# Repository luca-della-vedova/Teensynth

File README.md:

# Teensynth

The aim of the project is to create a companion board for MIDI compatible keyboards / electric pianos and augment them with commonly used / needed features such as:

* Midi recording: Sample and forward USB Midi signal and forward it to the host machine (or record in an SD card).
* Audio recording: Record Line out / Headphone out (for now only the latter is implemented) and stream it to the host through an Audio USB device interface.
* Midi synthesizer: Read MIDI files from SD card or receive MIDI commands from USB interface and synthesize them, as well as mix them with the audio signal (i.e. create a midi base and jam on it!)
* Implement pitch bend: For keyboards that support pitch bend MIDI commands but don't have a pitch wheel, create one with a joystick / potentiometer.

The board aims to be used in two ways:

### Standalone mode

All the recording outputs are to SD card, all the inputs (i.e. MIDI) are from SD card or firmware, control is done through hardware buttons and feedback to the user is through the Grove compatible I2C LCD display. 

### USB device mode

The device implements bidirectional MIDI (send the keyboard output to the host machine / synthesize the host machine's output) and Audio streaming to the host machine.
Streaming audio from the host machine to the onboard DAC should also be possible but is not a priority right now.

# Hardware

The hardware has been designed with kicad, it is a carrier board for  Teensy 4.1 and the Adafruit VS1053B breakout board.

# Firmware

The firmware has been developed with the Arduino / Teensyduino IDE, using external libraries (such as Adafruit VS1053B library) when necessary.

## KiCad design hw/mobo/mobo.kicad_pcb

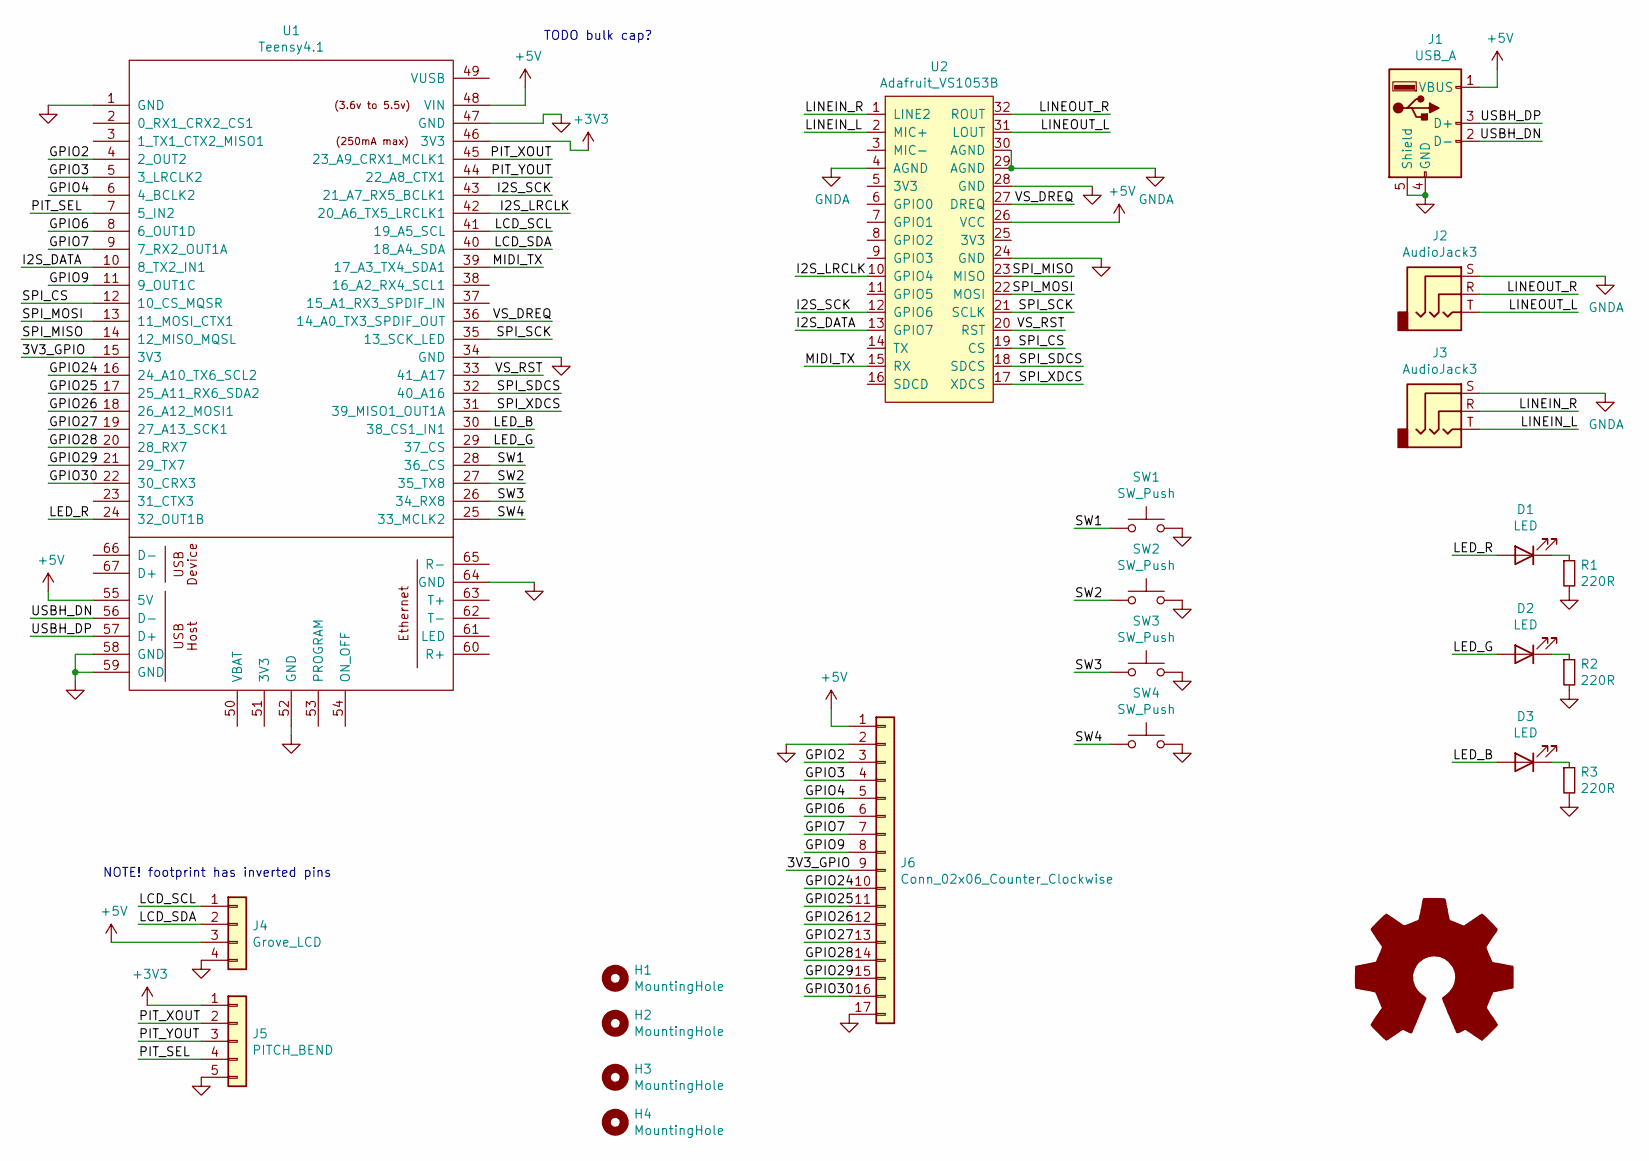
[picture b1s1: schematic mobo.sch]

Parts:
D1, D2, D3: LED; LED_1206_3216Metric_Pad1.42x1.75mm_HandSolder
H1, H2, H3, H4: MountingHole; MountingHole_3.2mm_M3
J1: USB_A; USB_A_Molex_67643_Horizontal
J2, J3: AudioJack3; Jack_3.5mm_CUI_SJ-3523-SMT_Horizontal
J4: Grove_LCD; PinHeader_1x04_P2.00mm_Horizontal
J5: PITCH_BEND; PinHeader_1x05_P2.54mm_Horizontal
J6: Conn_02x06_Counter_Clockwise; PinSocket_1x17_P2.54mm_Vertical
LOGO1: Logo_Open_Hardware_Large; OSHW-Symbol_13.4x12mm_SilkScreen
R1, R2, R3: 220R; R_1206_3216Metric_Pad1.30x1.75mm_HandSolder
SW1, SW2, SW3, SW4: SW_Push; SW_PUSH_6mm_H5mm
U1: Teensy4.1; Teensy41
U2: Adafruit_VS1053B

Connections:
+3V3: J5.1, U1.46 (3V3)
+5V: J1.1 (VBUS), J4.3, J6.1, U1.48 (VIN), U1.55 (5V), U2.26 (VCC)
/3V3_GPIO: J6.9, U1.15 (3V3)
/GPIO2: J6.3, U1.4 (2_OUT2)
/GPIO3: J6.4, U1.5 (3_LRCLK2)
/GPIO4: J6.5, U1.6 (4_BCLK2)
/GPIO6: J6.6, U1.8 (6_OUT1D)
/GPIO7: J6.7, U1.9 (7_RX2_OUT1A)
/GPIO9: J6.8, U1.11 (9_OUT1C)
/GPIO24: J6.10, U1.16 (24_A10_TX6_SCL2)
/GPIO25: J6.11, U1.17 (25_A11_RX6_SDA2)
/GPIO26: J6.12, U1.18 (26_A12_MOSI1)
/GPIO27: J6.13, U1.19 (27_A13_SCK1)
/GPIO28: J6.14, U1.20 (28_RX7)
/GPIO29: J6.15, U1.21 (29_TX7)
/GPIO30: J6.16, U1.22 (30_CRX3)
/I2S_DATA: U1.10 (8_TX2_IN1), U2.13 (GPIO7)
/I2S_LRCLK: U1.42 (20_A6_TX5_LRCLK1), U2.10 (GPIO4)
/I2S_SCK: U1.43 (21_A7_RX5_BCLK1), U2.12 (GPIO6)
/LCD_SCL: J4.1, U1.41 (19_A5_SCL)
/LCD_SDA: J4.2, U1.40 (18_A4_SDA)
/LED_B: D3.2 (A), U1.30 (38_CS1_IN1)
/LED_G: D2.2 (A), U1.29 (37_CS)
/LED_R: D1.2 (A), U1.24 (32_OUT1B)
/LINEIN_L: J3.T, U2.2 (MIC+)
/LINEIN_R: J3.R, U2.1 (LINE2)
/LINEOUT_L: J2.T, U2.31 (LOUT)
/LINEOUT_R: J2.R, U2.32 (ROUT)
/MIDI_TX: U1.39 (17_A3_TX4_SDA1), U2.15 (RX)
/PIT_SEL: J5.4, U1.7 (5_IN2)
/PIT_XOUT: J5.2, U1.45 (23_A9_CRX1_MCLK1)
/PIT_YOUT: J5.3, U1.44 (22_A8_CTX1)
/SPI_CS: U1.12 (10_CS_MQSR), U2.19 (CS)
/SPI_MISO: U1.14 (12_MISO_MQSL), U2.23 (MISO)
/SPI_MOSI: U1.13 (11_MOSI_CTX1), U2.22 (MOSI)
/SPI_SCK: U1.35 (13_SCK_LED), U2.21 (SCLK)
/SPI_SDCS: U1.32 (40_A16), U2.18 (SDCS)
/SPI_XDCS: U1.31 (39_MISO1_OUT1A), U2.17 (XDCS)
/SW1: SW1.1, U1.28 (36_CS)
/SW2: SW2.1, U1.27 (35_TX8)
/SW3: SW3.1, U1.26 (34_RX8)
/SW4: SW4.1, U1.25 (33_MCLK2)
/USBH_DN: J1.2 (D-), U1.56 (D-)
/USBH_DP: J1.3 (D+), U1.57 (D+)
/VS_DREQ: U1.36 (14_A0_TX3_SPDIF_OUT), U2.27 (DREQ)
/VS_RST: U1.33 (41_A17), U2.20 (RST)
GND: J1.4 (GND), J1.5 (Shield), J4.4, J5.5, J6.2, J6.17, R1.2, R2.2, R3.2, SW1.2, SW2.2, SW3.2, SW4.2, U1.1 (GND), U1.34 (GND), U1.47 (GND), U1.52 (GND), U1.58 (GND), U1.59 (GND), U1.64 (GND), U2.24 (GND), U2.28 (GND)
GNDA: J2.S, J3.S, U2.4 (AGND), U2.29 (AGND), U2.30 (AGND)
unnamed: D1.1 (K), R1.1
unnamed: D2.1 (K), R2.1
unnamed: D3.1 (K), R3.1

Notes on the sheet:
TODO bulk cap?
NOTE! footprint has inverted pins

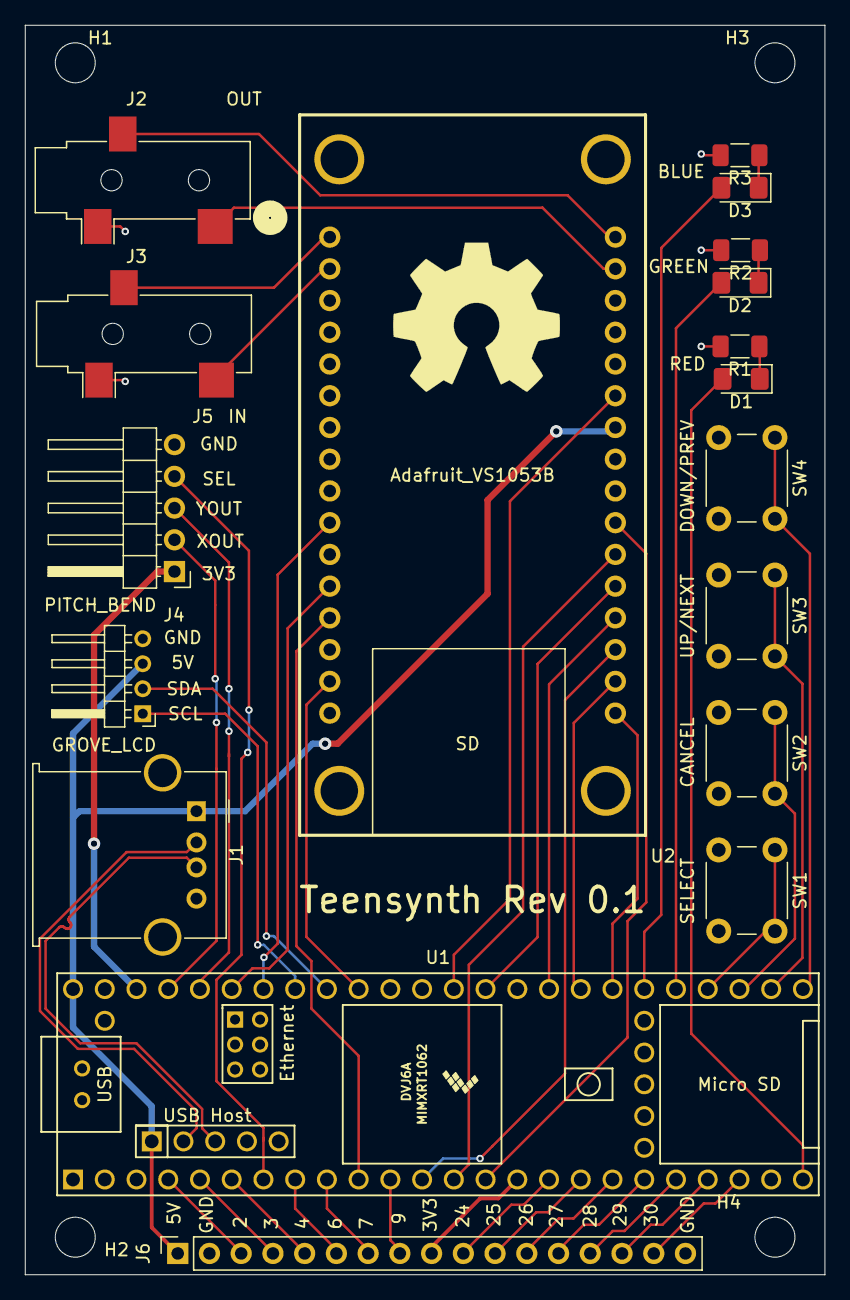
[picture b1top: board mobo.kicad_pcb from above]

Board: 2 copper layers, 64.0 x 100.0 mm, 23 parts (0 on the bottom side), 51 nets.

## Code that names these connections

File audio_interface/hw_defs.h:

// Defines for VS1053B board
#define VS1053_RESET  41      // VS1053 reset pin (output)
#define VS1053_CS     10     // VS1053 chip select pin (output)
#define VS1053_DCS    93      // VS1053 Data/command select pin (output)

#define VS1053_CARDCS 40     // Card chip select pin
#define VS1053_DREQ 14       // VS1053 Data request, ideally an Interrupt pin

#define VS1053_MIDI Serial4

// LEDS
#define LED_R 32
#define LED_G 37
#define LED_B 38

#define BEAT_LED LED_B
#define READY_LED LED_G
#define SD_ERROR_LED LED_R
#define SMF_ERROR_LED LED_R

// Buttons
#define SW_SELECT 36
#define SW_CANCEL 35
#define SW_NEXT 34
#define SW_PREV 33

// Pitch bend pot
#define POT_X 9
#define POT_Y 8

// Grove LCD I2C, just default I2C
#define LCD_I2C Wire

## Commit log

2020-11-15 First commit, admixer added
2020-11-15 Refactor plugin code into separate header
2020-11-15 First commit, pitch bend and VS1052 basic implem
2020-11-15 Changed root directory
2020-11-15 Added hello world with RT-midi
2020-11-22 Add kicad libraries for board
2020-11-22 Rev 0.1 sent for fab
2020-11-22 Some docs / board rendering
2020-11-22 Fix image file path
2020-11-28 Add schematic printout
2020-11-30 Added vs1053 mono admix plugin
2020-11-30 Skeleton of MIDI playback and start LCD library
